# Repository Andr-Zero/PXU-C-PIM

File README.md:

# PXU USB-C Power Input Module (PIM)
## _Power your OG Xbox via a USB Charger!_

This is based off the [SparkFun USB-C Power Delivery Board](https://github.com/sparkfun/Power_Delivery_Board-USB-C)

##### Disclaimer!
- I'm not an Electrical Engineer. Just wanted to make something cool and challenge myself.
- The OEM power supply can hold a potentially dangerous charge even after being unplugged for a large period of time!
- Your USB-C Cable MUST be capable of handling 100w! Lot out here that’s only 65w and most don’t have markings saying what their limits are. 
- You're on your own, I'm not responsible for injury or damages. 

##### TODO
- Photos
- Install instruction
- Upload Arduino code for programming
- Upload board and design files
- Explain header, programming, and LEDs
- Update License, assume same as Sparkfuns for now, attrubution specifically. 

##### FAQ
- What chargers work?  
  I dont have a definitive list. Any 100w charger *should* work. I tested with an Anker 100w I got off Amazon and have had no issues.
- Does it have to be a 100w charger?  
   At a minimum, YES! There's a lot of 65w chargers out there and they simply not enough to power a *stock* console.
- I'm plugging in my charger but nothing is working.  
   The charger has to be able to negotiate with the PIM saying it can do ~100w at 20v, otherwise the PIM refuses to pass power.
- My USB charger is warm when running the console, is that normal?  
   Depends on the charger, mine does and with anything I use it with. Apperently the GaN chargers run cooler? I've yet to verify myself.
- My USB-C Cable is hot or has melted down!  
   It wasn’t rated for 100w. MUST use a cable that’s rated for 100w.
- Is this "Complete"
   No it not completed. There's still several things that need addressed.

##### Known Issues
-AC adapters that support PPS (Programgamable Power Supply) seems to have issues.

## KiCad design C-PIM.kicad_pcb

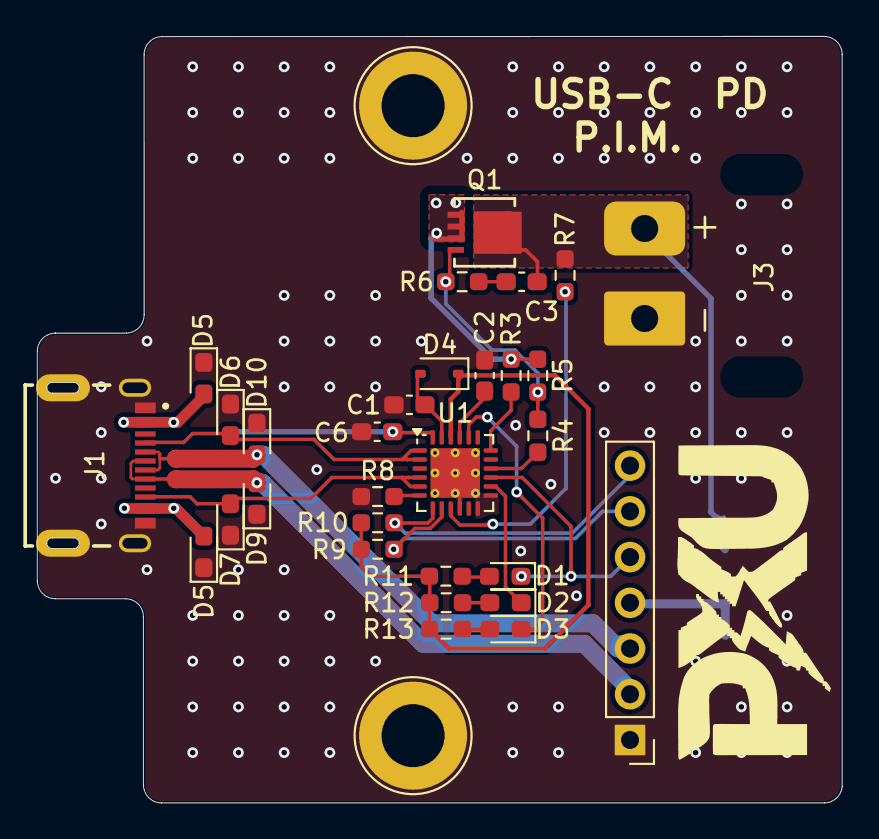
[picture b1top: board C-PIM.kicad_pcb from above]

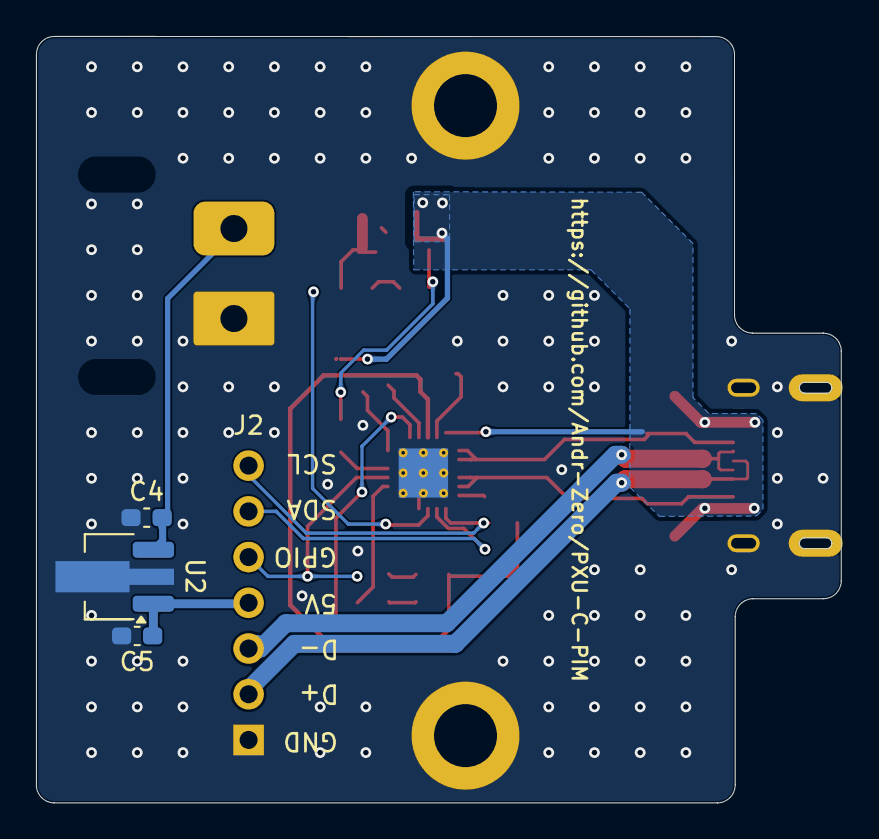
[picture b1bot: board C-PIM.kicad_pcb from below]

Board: 2 copper layers, 44.7 x 42.6 mm, 33 parts (4 on the bottom side), 25 nets.

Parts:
C1, C2, C3, C4, C5, C6: 1uF 25v; C_0603_1608Metric_Pad1.08x0.95mm_HandSolder
D1: RED; LED_0603_1608Metric_Pad1.05x0.95mm_HandSolder
D2: Green; LED_0603_1608Metric_Pad1.05x0.95mm_HandSolder
D3: Yellow; LED_0603_1608Metric_Pad1.05x0.95mm_HandSolder
D4: BAT60A; D_SOD-323
D5, D5#2, D6, D7, D9, D10: 24V; D_0603_1608Metric_Pad1.05x0.95mm_HandSolder
J1: USB4215-03-A_REVA; GCT_USB4215-03-A_REVA
J2: CONN_07NO_SILK; PinHeader_1x07_P2.54mm_Vertical
J3: Conn_01x02_Pin; AMASS_XT30PW-M_1x02_P2.50mm_Horizontal
Q1: 9A/30V/15mΩ; POWERFLAT_3P3X3P3_STM
R3, R7, R11, R12, R13: 1k; R_0603_1608Metric_Pad0.98x0.95mm_HandSolder
R4: 22k; R_0603_1608Metric_Pad0.98x0.95mm_HandSolder
R5, R8: 100k; R_0603_1608Metric_Pad0.98x0.95mm_HandSolder
R6: 100r; R_0603_1608Metric_Pad0.98x0.95mm_HandSolder
R9, R10: 4.7k; R_0603_1608Metric_Pad0.98x0.95mm_HandSolder
U1: STUSB4500; QFN-24-1EP_4x4mm_P0.5mm_EP2.75x2.75mm_ThermalVias
U2: AP7375Q-50Y-13; SOT-89-3_Handsoldering

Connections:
5vReg: C5.1, J2.4, U2.3 (VI)
/CC1: D6.2 (C), J1.A5 (CC1), U1.1 (CC1DB), U1.2 (CC1)
/CC2: D7.2 (C), J1.B5 (CC2), U1.4 (CC2), U1.5 (CC2DB)
/D+: D9.2 (C), J1.A6 (DP1), J1.B6 (DP2), J2.2
/D-: D10.2 (C), J1.A7 (DN1), J1.B7 (DN2), J2.3
/GPIO: D1.1 (K), J2.5, U1.15 (GPIO)
/POWER_PDO2: D3.1 (K), U1.20 (POWER_OK2)
/POWER_PDO3: D2.1 (K), U1.14 (POWER_OK3)
GND: C1.2, C2.2, C4.2, C5.2, C6.2, D5.1 (A), D5#2.1 (A), D6.1 (A), D7.1 (A), D9.1 (A), D10.1 (A), J1.A1_B12 (GND_A), J1.B1_A12 (GND_B), J1.SH1 (SHIELD), J1.SH2 (SHIELD), J2.1, J3.2, R8.1, U1.10 (GND), U1.12 (ADDR0), U1.13 (ADDR1), U1.25 (GND), U2.2 (GND)
unnamed: C3.2, R6.2
unnamed: D1.2 (A), R11.1
unnamed: D2.2 (A), R12.1
unnamed: D3.2 (A), R13.1
unnamed: C1.1, D4.2 (A), U1.23 (VREG_2V7)
unnamed: Q1.4 (G), R4.2, R5.1, R6.1
unnamed: R7.2, U1.9 (DISCH)
unnamed: R8.2, U1.6 (RESET)
unnamed: J2.7, R10.1, U1.7 (SCL)
unnamed: J2.6, R9.1, U1.8 (SDA)
unnamed: R4.1, U1.16 (VBUS_EN_SNK)
unnamed: R3.1, U1.18 (VBUS_VS_DISCH)
unnamed: C2.1, U1.21 (VREG_1V2)
VDD: D4.1 (K), R9.2, R10.2, R11.2, R12.2, R13.2, U1.22 (VSYS)
VIN: C6.1, D5.2 (C), D5#2.2 (C), J1.A4_B9 (VBUS_A), J1.B4_A9 (VBUS_B), Q1.1 (S), Q1.2 (S), Q1.3 (S), R3.2, R5.2, U1.24 (VDD)
VSNK: C3.1, C4.1, J3.1, Q1.5 (D), Q1.6 (D), Q1.7 (D), Q1.8 (D), R7.1, U2.1 (VO)

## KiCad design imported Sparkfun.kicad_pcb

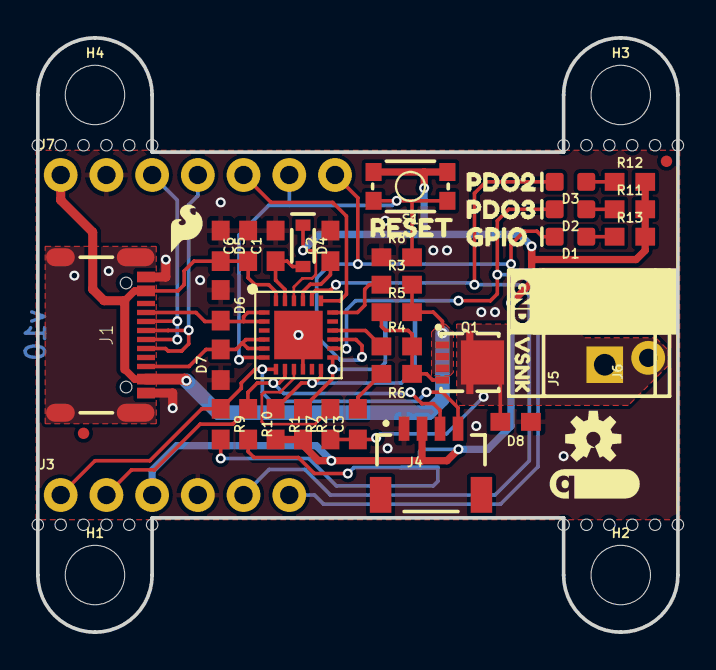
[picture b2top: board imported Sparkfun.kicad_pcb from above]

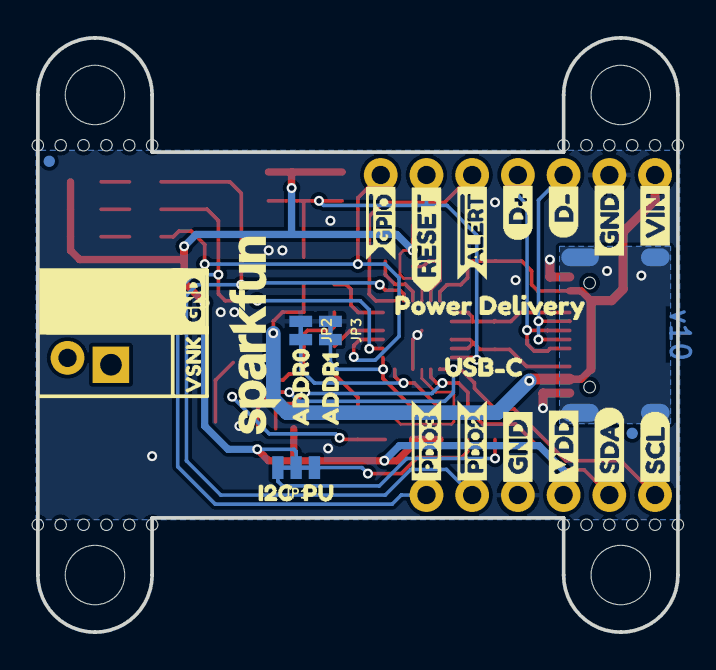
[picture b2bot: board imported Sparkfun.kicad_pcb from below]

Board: 2 copper layers, 35.6 x 33.0 mm, 101 parts (27 on the bottom side), 30 nets.

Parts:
@HOLE0, @HOLE1, @HOLE2, @HOLE3, @HOLE4, @HOLE5, @HOLE6, @HOLE7, @HOLE8, @HOLE9, @HOLE10, @HOLE11, @HOLE12, @HOLE13, @HOLE14, @HOLE15, @HOLE16, @HOLE17, @HOLE18, @HOLE19, @HOLE20, @HOLE21, @HOLE22, @HOLE23: (no value)
C1, C2, C6: 1.0uF; 0603
C3: 0.1uF; 0603
D1: BLUE; LED-0603
D2: Yellow; LED-0603
D3: GREEN; LED-0603
D4: BAT60A; SOD-323
D5, D6, D7, D8: 24V; 0603
FD1, FD2, FD3, FD4: FIDUCIALUFIDUCIAL; FIDUCIAL-MICRO
FRAME1: FRAME-LETTER; CREATIVE_COMMONS
H1, H2, H3, H4: STAND-OFF
J1: USB-C-16P
J3: 1X06_NO_SILK
J4: QWIIC; JST04_1MM_RA
J5: SCREWTERMINAL-3.5MM-2
J6: 1X02_NO_SILK
J7: 1X07_NO_SILK
JP1: SMT-JUMPER_3_2-NC_TRACE_NO-SILK
JP2, JP3: SMT-JUMPER_2_NC_TRACE_NO-SILK
LOGO1: OSHW-LOGOS; OSHW-LOGO-S
LOGO2: SFE_LOGO_NAME.1_INCH; SFE_LOGO_NAME_.1
LOGO3: QWIIC_LOGO_5MM; QWIIC_5MM
Q1: 9A/30V/15mΩ; 8-POWERVDFN-3X3
R1, R2, R5, R8: 100k; 0603
R3, R7, R11, R12, R13: 1k; 0603
R4: 22k; 0603
R6: 100; 0603
R9, R10: 2.2k; 0603
S1: TACTILE_SWITCH_SMD_4.6X2.8MM
U1: STUSB4500; QFN-24
U$1: VDD2
U$2, U$11: GND6
U$3: SDA11
U$4: SCL12
U$5: #GPIO0
U$7: D#8
U$8: D#7
U$9: USB#C1
U$10: RESET10
U$12: VIN6
U$13: I2C2
U$14: PU3
U$15: ADDR00
U$16: ADDR11
U$17: RESET7
U$18: GPIO1
U$19: PDO24
U$20: PDO35
U$21, U$24: VSNK1
U$22, U$23: GND0
U$25: SFE_LOGO_FLAME_.1
U$26: #ALERT0
U$27: _POWER_DELIVERY2
U$29: #PDO20
U$30: #PDO31

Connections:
1.2V: C2.1, U1.P$21
2.7V: C1.1, D4.A, U1.P$23
ADDR0: JP2.2, R1.1, U1.P$12
ADDR1: JP3.2, R2.1, U1.P$13
CC1: D6.2, J1.A5, U1.P$1, U1.P$2
CC2: D7.2, J1.B5, U1.P$4, U1.P$5
D+: J1.A6, J1.B6, J7.4
D-: J1.A7, J1.B7, J7.3
DISCH: R7.2, U1.P$9
EN_SNK: R4.1, U1.P$16
GND: C1.2, C2.2, C6.2, D5.1, D6.1, D7.1, D8.1, J1.GND, J1.GND2, J3.4, J4.1, J5.2, J6.2, J7.2, JP2.1, JP3.1, R8.1, U1.P$10, U1.P$25
GPIO: D1.C, J7.7, U1.P$15
unnamed: D2.A, R11.1
unnamed: D3.A, R12.1
unnamed: JP1.3, R9.2
unnamed: JP1.1, R10.2
unnamed: Q1.4, R4.2, R5.1, R6.1
unnamed: C3.2, R6.2
unnamed: D1.A, R13.1
POWER_PDO2: D3.C, J3.5, U1.P$20
POWER_PDO3: D2.C, J3.6, U1.P$14
RESET: J7.6, R8.2, S1.3, S1.4, U1.P$6
SCL: J3.1, J4.4, R9.1, U1.P$7
SDA: J3.2, J4.3, R10.1, U1.P$8
SHIELD: J1.SHLD1, J1.SHLD2, J1.SHLD3, J1.SHLD4, J1.SHLD5, J1.SHLD6, J1.SHLD7, J1.SHLD8
VBUS_VS_DISCH: R3.1, U1.P$18
VDD: D4.C, J3.3, J4.2, JP1.2, R1.2, R2.2, R11.2, R12.2, R13.2, S1.1, S1.2, U1.P$22
VIN: C6.1, D5.2, J1.VBUS1, J1.VBUS2, J7.1, Q1.1, Q1.2, Q1.3, R3.2, R5.2, U1.P$24
VSNK: C3.1, D8.2, J5.1, J6.1, Q1.5@1, Q1.5@2, Q1.5@3, R7.1
~ALERT: J7.5, U1.P$19

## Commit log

2025-03-30 Create README.md
    init
2025-03-30 Update README.md
    damn markdown
2025-03-31 Update README.md
    linked sparkfun's repo
2025-08-04 Initial release board.
    There are several changes required, mostly improve the TVS', smaller footprint, and balance the voltage copper pours.
2025-11-09 Rev2 of the USB Module
2025-11-09 Clean Upload
2025-11-21 RE-Attach Readme
    Failed to pay attention on how I was pushing.
2025-11-21 Upload of license.md

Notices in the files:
parts and their libraries:
Released under the Creative Commons Attribution Share-Alike 4.0 License
https://creativecommons.org/licenses/by-sa/4.0
